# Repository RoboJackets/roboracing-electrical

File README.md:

# RoboRacing Electrical
This is a repository for the RoboJackets' RoboRacing Electrical team.

## rigatoni
Contains current files associated with Rigatoni.

## archive
Contains old files no longer in use on the current robots.

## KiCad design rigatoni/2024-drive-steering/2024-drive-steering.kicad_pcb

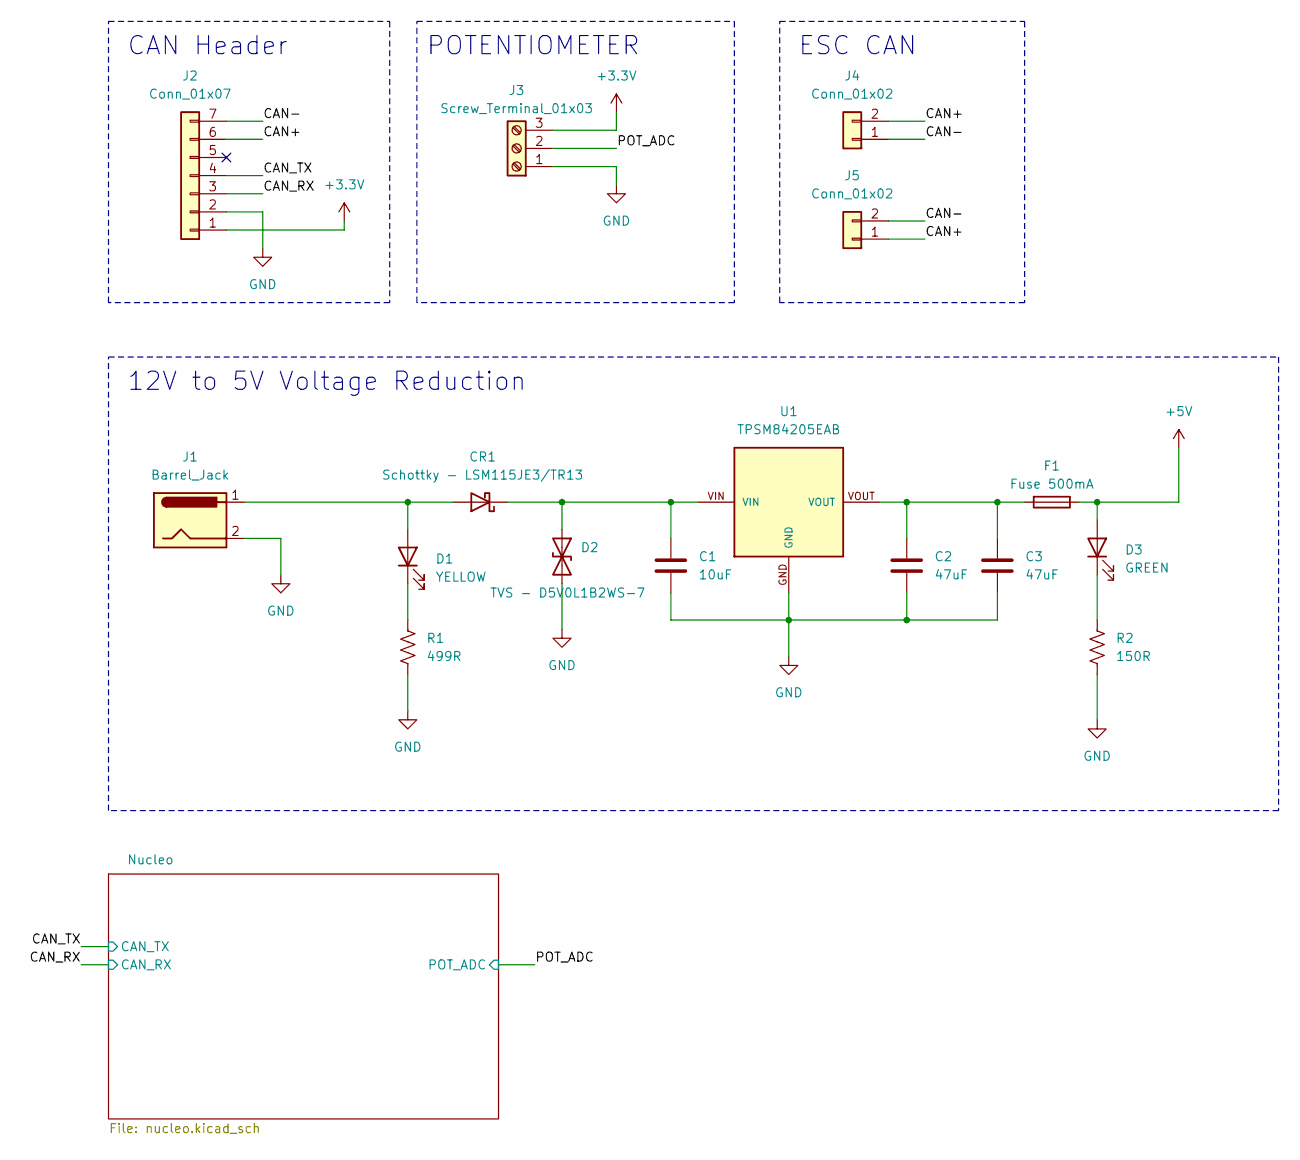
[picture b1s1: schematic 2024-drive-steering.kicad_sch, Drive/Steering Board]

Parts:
C1: 10uF; C_0805_2012Metric_Pad1.18x1.45mm_HandSolder; Part Name CL21A106KOQNNNE; DigiKey Part Number 1276-1096-1-ND
C2, C3: 47uF; C_1210_3225Metric_Pad1.33x2.70mm_HandSolder; Part Name CL32A476KOJNNNE; DigiKey Part Number 1276-3376-1-ND
CR1: Schottky - LSM115JE3/TR13; DO-214BA_MCH; Part Description Diode 15 V 1A Surface Mount DO-214BA; DigiKey Part Number 150-LSM115JE3/TR13CT-ND
D1: YELLOW; LED_0603_1608Metric_Pad1.05x0.95mm_HandSolder; Part Name 150060YS75000; DigiKey Part Number 732-4981-1-ND
D2: TVS - D5V0L1B2WS-7; D_SOD-323_HandSoldering; Part Description 14V Clamp 6A (8/20µs) Ipp Tvs Diode Sur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; DigiKey Part Number D5V0L1B2WS-7DICT-ND
D3: GREEN; LED_0603_1608Metric_Pad1.05x0.95mm_HandSolder; Part Name 150060GS75000; DigiKey Part Number 732-4971-1-ND
F1: Fuse 500mA; Fuse_0603_1608Metric_Pad1.05x0.95mm_HandSolder; Part Name C2Q 500; DigiKey Part Number 507-1089-1-ND
J1: Barrel_Jack; CUI_PJ-037A; Part Name PJ-037A; DigiKey Part Number CP-037A-ND
J2: Conn_01x07; CAN_Header
J3: Screw_Terminal_01x03; 282837-3_TYC; Part Name 282837-3; DigiKey Part Number A113321-ND
J4, J5: Conn_01x02; JST_PH_B2B-PH-K_1x02_P2.00mm_Vertical
R1: 499R; R_0603_1608Metric_Pad0.98x0.95mm_HandSolder; Part Name RC0603FR-07499RL; DigiKey Part Number 311-499HRCT-ND
R2: 150R; R_0603_1608Metric_Pad0.98x0.95mm_HandSolder; Part Name AC0603FR-07150RL; DigiKey Part Number YAG3568CT-ND
U1: TPSM84205EAB; Part Description Linear Regulator Replacement DC DC Conv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; DigiKey Part Number 296-47074-ND

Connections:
+3.3V: J2.1, J3.3; also elsewhere on the board
+5V: D3.2 (A), F1.1; also elsewhere on the board
/CAN+: J2.6, J4.2, J5.1
/CAN-: J2.7, J4.1, J5.2
/CAN_RX: J2.3; also elsewhere on the board
/CAN_TX: J2.4; also elsewhere on the board
/POT_ADC: J3.2; also elsewhere on the board
GND: C1.2, C2.2, C3.2, D2.2 (A2), J1.2, J2.2, J3.1, R1.1, R2.2, U1.GND; also elsewhere on the board
unnamed: C2.1, C3.1, F1.2, U1.VOUT
unnamed: CR1.2 (A), D1.2 (A), J1.1
unnamed: C1.1, CR1.1 (K), D2.1 (A1), U1.VIN
unnamed: D1.1 (K), R1.2
unnamed: D3.1 (K), R2.1

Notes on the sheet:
12V to 5V Voltage Reduction
ESC CAN
POTENTIOMETER
CAN Header

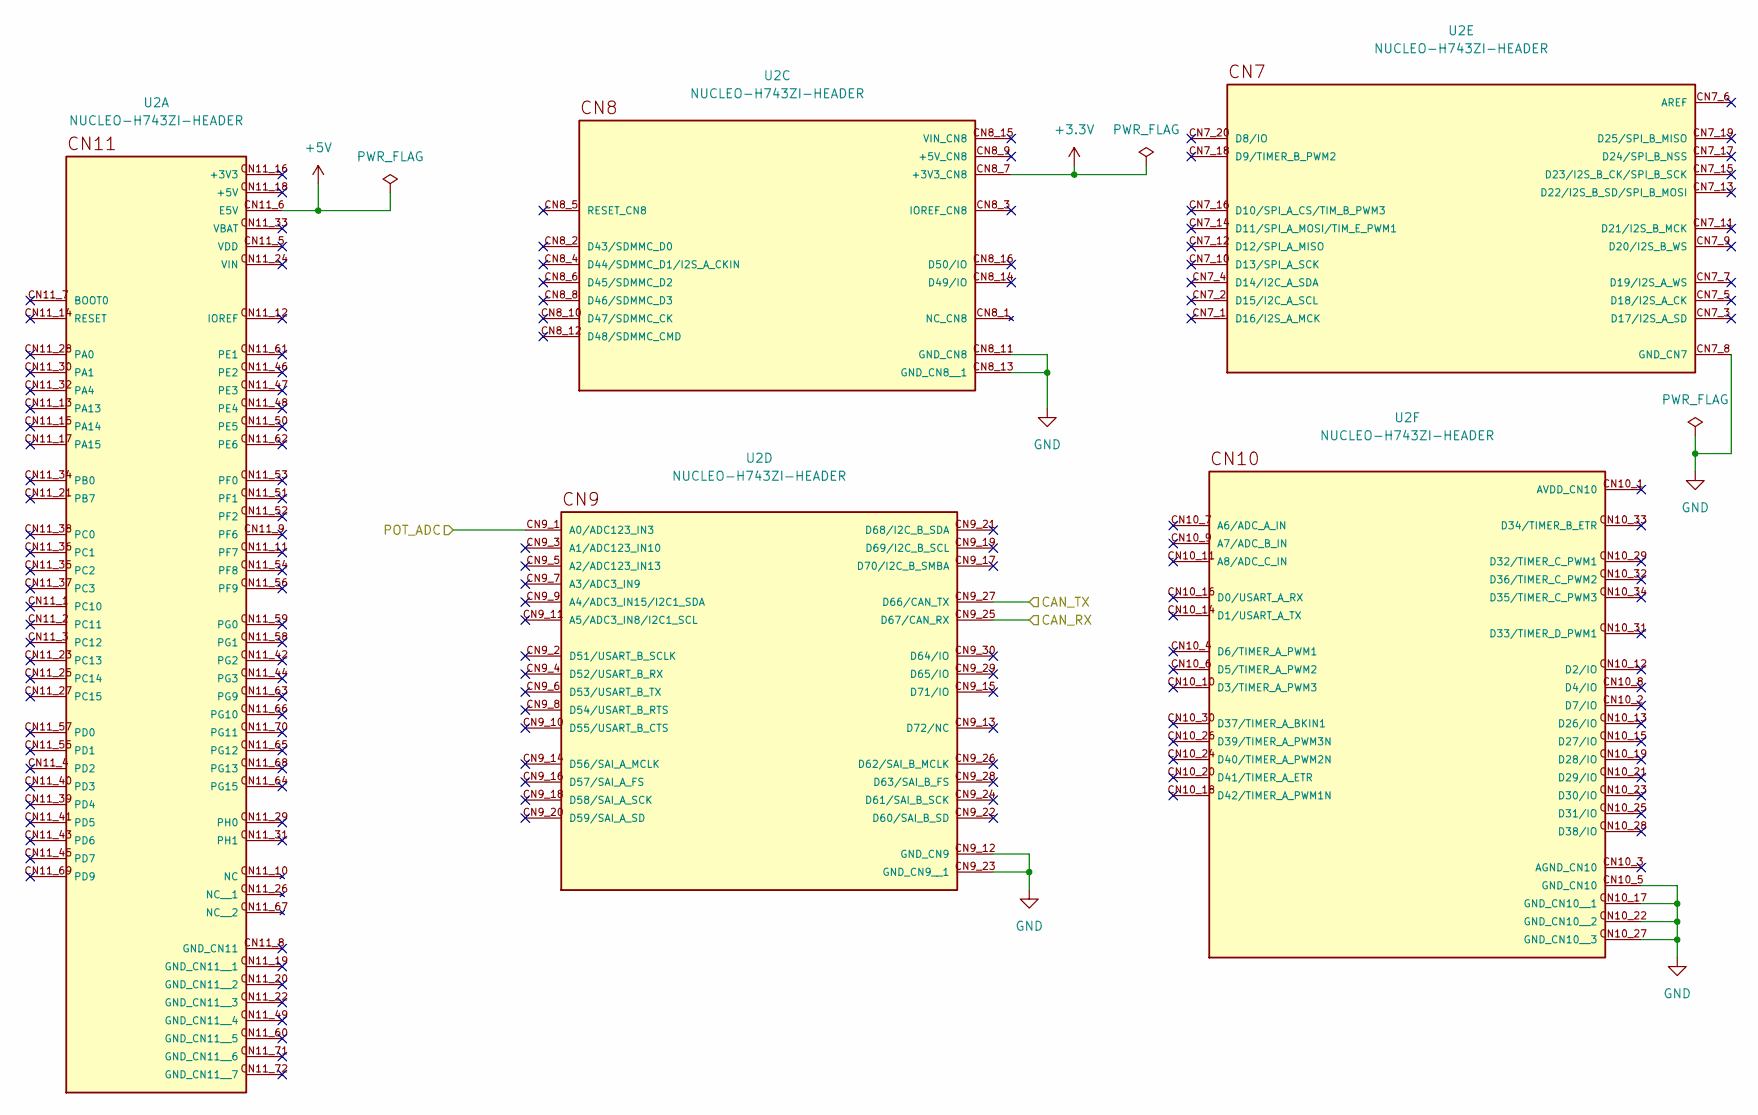
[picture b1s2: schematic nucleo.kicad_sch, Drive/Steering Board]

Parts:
U2: NUCLEO-H743ZI-HEADER; Custom-Nucleo144-Header; PARTREV 8

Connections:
+3.3V: U2.CN8_7 (+3V3_CN8); also elsewhere on the board
+5V: U2.CN11_6 (E5V); also elsewhere on the board
/CAN_RX: U2.CN9_25 (D67/CAN_RX); also elsewhere on the board
/CAN_TX: U2.CN9_27 (D66/CAN_TX); also elsewhere on the board
/POT_ADC: U2.CN9_1 (A0/ADC123_IN3); also elsewhere on the board
GND: U2.CN7_8 (GND_CN7), U2.CN8_11 (GND_CN8), U2.CN8_13 (GND_CN8__1), U2.CN9_12 (GND_CN9), U2.CN9_23 (GND_CN9__1), U2.CN10_5 (GND_CN10), U2.CN10_17 (GND_CN10__1), U2.CN10_22 (GND_CN10__2), U2.CN10_27 (GND_CN10__3); also elsewhere on the board

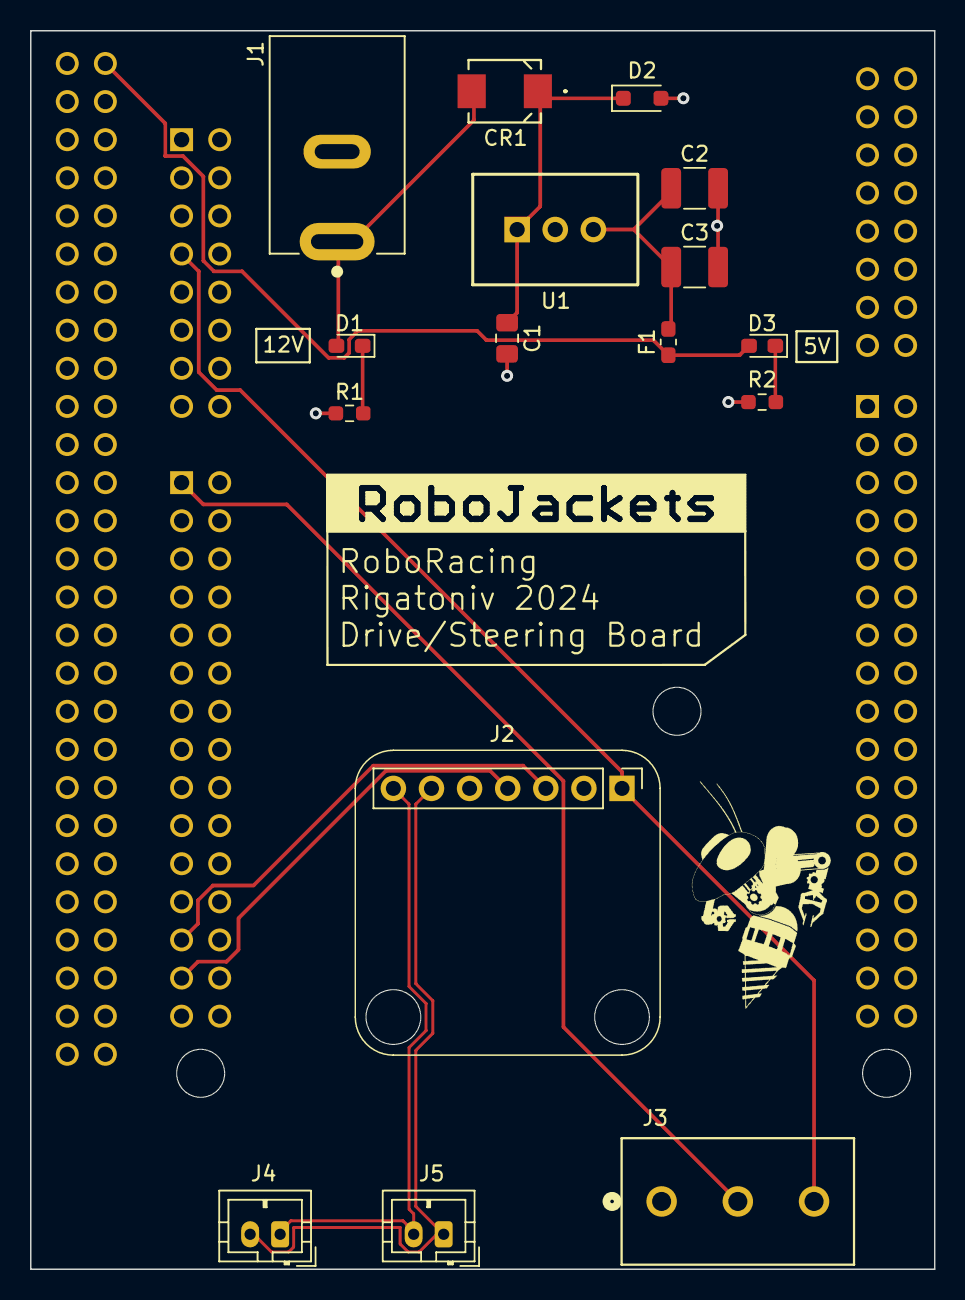
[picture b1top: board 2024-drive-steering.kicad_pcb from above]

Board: 2 copper layers, 60.2 x 82.5 mm, 17 parts (0 on the bottom side), 13 nets.

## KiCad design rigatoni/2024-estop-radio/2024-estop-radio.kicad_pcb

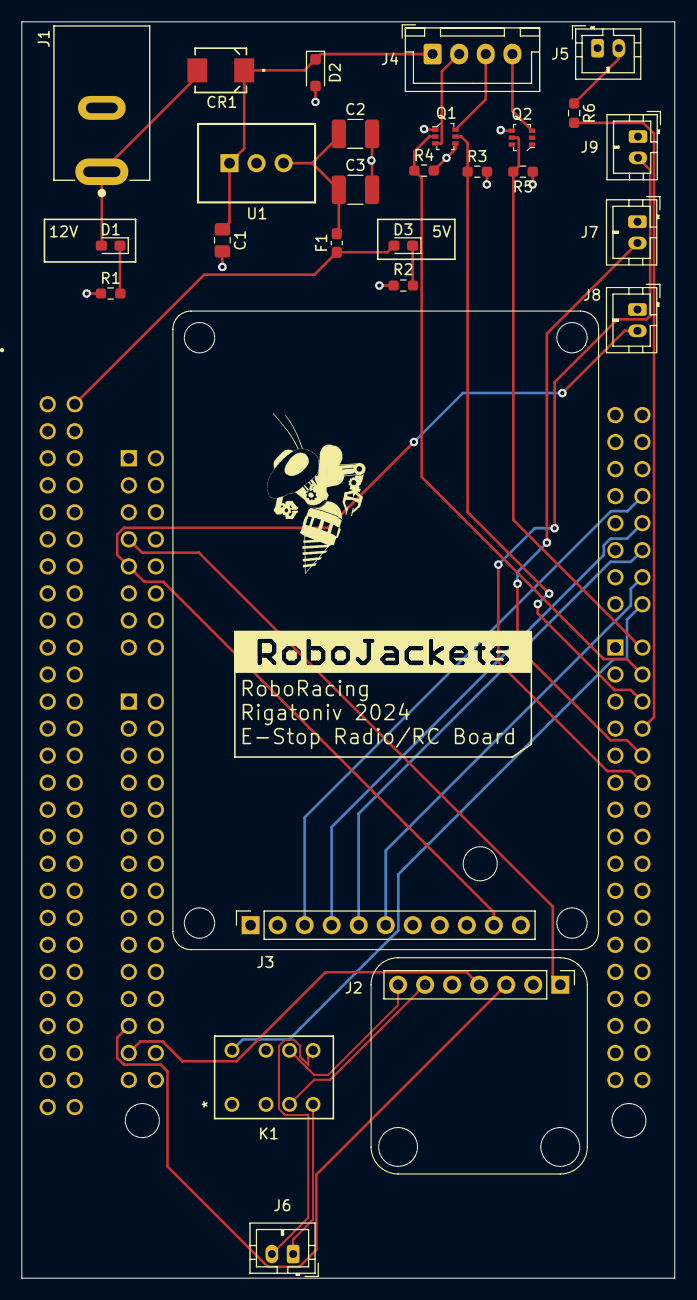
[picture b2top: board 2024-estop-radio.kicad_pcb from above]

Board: 2 copper layers, 61.4 x 118.1 mm, 28 parts (0 on the bottom side), 30 nets.

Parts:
C1: 10uF; C_0805_2012Metric_Pad1.18x1.45mm_HandSolder
C2, C3: 47uF; C_1210_3225Metric_Pad1.33x2.70mm_HandSolder
CR1: Schottky - LSM115JE3/TR13; DO-214BA_MCH
D1: YELLOW; LED_0603_1608Metric_Pad1.05x0.95mm_HandSolder
D2: TVS - D5V0L1B2WS-7; D_SOD-323_HandSoldering
D3: GREEN; LED_0603_1608Metric_Pad1.05x0.95mm_HandSolder
F1: Fuse 500mA; Fuse_0603_1608Metric_Pad1.05x0.95mm_HandSolder
J1: Barrel_Jack; CUI_PJ-037A
J2: Conn_01x07; CAN_Header
J3: Conn_01x11; E-Stop_Radio
J4: Conn_01x04; JST_XH_B4B-XH-A_1x04_P2.50mm_Vertical
J5, J6, J7, J8, J9: Conn_01x02; JST_PH_B2B-PH-K_1x02_P2.00mm_Vertical
K1: AGQ20003; RELAY_AGQ_PAN
Q1, Q2: BSS138DW-7-F; SOT-363
R1, R6: 499R; R_0603_1608Metric_Pad0.98x0.95mm_HandSolder
R2: 150R; R_0603_1608Metric_Pad0.98x0.95mm_HandSolder
R3, R4, R5: 10kR; R_0603_1608Metric_Pad0.98x0.95mm_HandSolder
U1: TPSM84205EAB
U2: NUCLEO-H743ZI-HEADER; Custom-Nucleo144-Header

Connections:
+3.3V: J2.1, U2.CN8_7 (+3V3_CN8)
+5V: J3.10, J8.2, U2.CN8_9 (+5V_CN8)
+12V: C1.1, CR1.1 (K), D2.1 (A1), J4.1, U1.VIN
/CAN_RX: J2.3, U2.CN9_25 (D67/CAN_RX)
/CAN_Relay: K1.8, U2.CN7_20 (D8/IO)
/CAN_TX: J2.4, U2.CN9_27 (D66/CAN_TX)
/Drive_Enable: J3.3, U2.CN7_12 (D12/SPI_A_MISO)
/Drive_RC: J9.2, U2.CN10_12 (D2/IO)
/E5V: D3.2 (A), F1.1, U2.CN11_6 (E5V)
/Estop_CAN+: J2.6, K1.3
/Estop_CAN-: J2.7, K1.6
/HV_Enable: R6.2, U2.CN10_8 (D4/IO)
/SW_CAN+: J6.1, K1.4
/SW_CAN-: J6.2, K1.5
/Safe_Estop: J3.6, U2.CN7_18 (D9/TIMER_B_PWM2)
/Stack_Light1: J4.2, Q1.3 (D1)
/Stack_Light2: J4.3, Q1.6 (D2)
/Stack_Light3: J4.4, Q2.3 (D1)
/Stack_MCU1: Q1.5 (G1), R3.1, U2.CN10_6 (D5/TIMER_A_PWM2)
/Stack_MCU2: Q1.2 (G2), R4.1, U2.CN10_4 (D6/TIMER_A_PWM1)
/Stack_MCU3: Q2.5 (G1), R5.2, U2.CN10_2 (D7/IO)
/Start_Estop: J3.5, U2.CN7_16 (D10/SPI_A_CS/TIM_B_PWM3)
/Steering_Enable: J3.4, U2.CN7_14 (D11/SPI_A_MOSI/TIM_E_PWM1)
/Steering_RC: J7.2, U2.CN10_10 (D3/TIMER_A_PWM3)
GND: C1.2, C2.2, C3.2, D2.2 (A2), J1.2, J2.2, J3.1, J3.11, J5.1, J7.1, J8.1, J9.1, K1.1, Q1.1 (S2), Q1.4 (S1), Q2.4 (S1), R1.1, R2.2, R3.2, R4.2, R5.1, U1.GND, U2.CN7_8 (GND_CN7), U2.CN8_11 (GND_CN8), U2.CN8_13 (GND_CN8__1), U2.CN9_12 (GND_CN9), U2.CN9_23 (GND_CN9__1), U2.CN10_5 (GND_CN10), U2.CN10_17 (GND_CN10__1), U2.CN10_22 (GND_CN10__2), U2.CN10_27 (GND_CN10__3)
unnamed: C2.1, C3.1, F1.2, U1.VOUT
unnamed: CR1.2 (A), D1.2 (A), J1.1
unnamed: D1.1 (K), R1.2
unnamed: D3.1 (K), R2.1
unnamed: J5.2, R6.1

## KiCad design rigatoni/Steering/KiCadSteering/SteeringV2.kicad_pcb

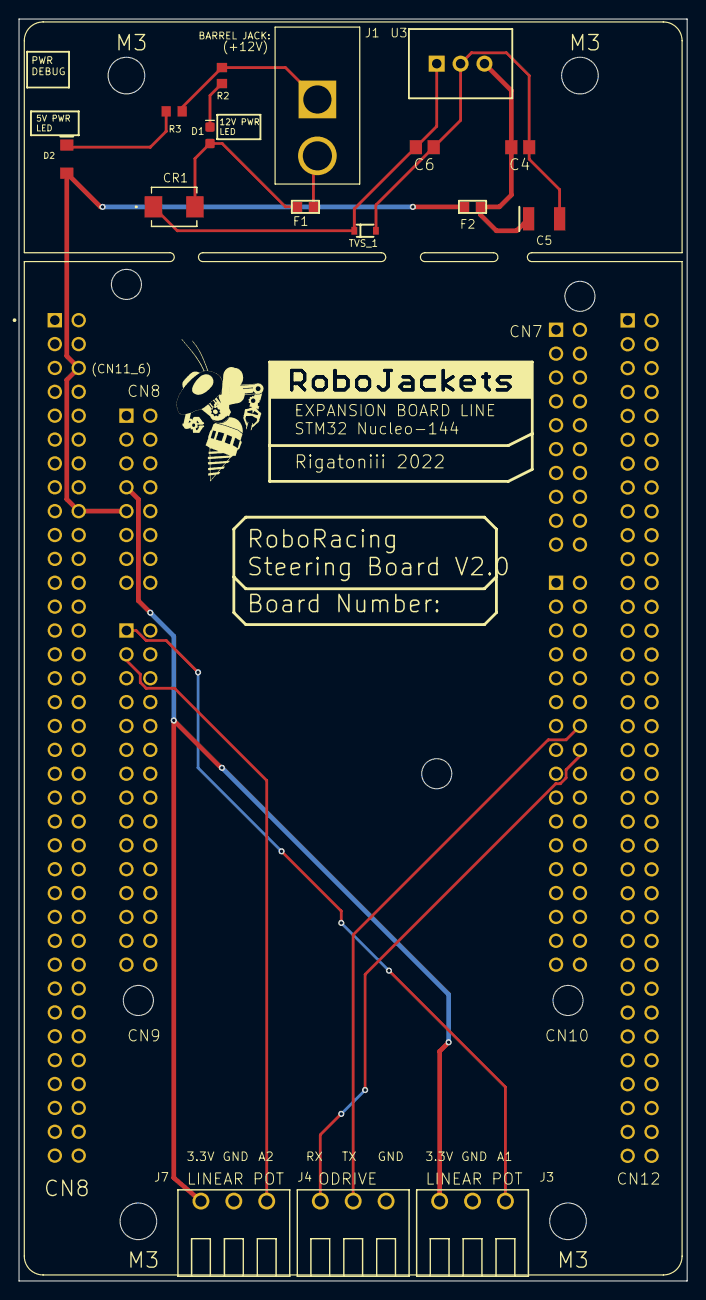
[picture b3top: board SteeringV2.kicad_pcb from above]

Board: 2 copper layers, 71.1 x 134.3 mm, 23 parts (0 on the bottom side), 13 nets.

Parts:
C4: 0.1uF; C0805
C5: 47uF; EIA3528
C6: 10uF; C0805
CR1: LSM115JE3/TR13; DO-214BA_MCH
D1: Yellow; LED-0603
D2: GREEN; LED-1206
F1: 630mA; F0603
F2: 1.875A; F0603
J1: PJ-037A
J3, J4, J7: PCB_SCREW_TERM_3; SCREW_TERMINAL_PCB_CONN_3_POLE
R2: 500R; R0603
R3: 147R; R0603
TVS_1: D5V0L1B2WS-7; SOD-323
U2: NUCLEO-H743ZI-HEADER; MODULE_NUCLEO-H743ZI
U3: TPSM84205EAB
U$1: ROBOBUZZ_0.8X
U$2, U$3, U$4, U$5: STANDOFF-HOLE
U$6: ROBOJACKETS

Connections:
5V_MAIN: C4.1, C5.A, F2.1, U3.VOUT
+3.3V: J3.1, J7.1, U2.CN8_7
+5V: D2.A, F2.2, U2.CN8_9, U2.CN11_6, U2.CN11_18
GND: C4.2, C5.C, C6.2, J1.P$1, J3.2, J4.3, J7.2, R2.1, R3.1, TVS_1.A, U2.CN7_8, U2.CN8_11, U2.CN8_13, U2.CN9_12, U2.CN9_23, U2.CN10_3, U2.CN10_5, U2.CN10_17, U2.CN10_22, U2.CN10_27, U2.CN11_8, U2.CN11_19, U2.CN11_20, U2.CN11_22, U2.CN11_49, U2.CN11_60, U2.CN11_71, U2.CN11_72, U2.CN12_9, U2.CN12_20, U2.CN12_32, U2.CN12_39, U2.CN12_54, U2.CN12_63, U2.CN12_71, U2.CN12_72, U3.GND
LINPOT_A1: J3.3, U2.CN9_1
LINPOT_A2: J7.3, U2.CN9_3
unnamed: CR1.2, D1.A, F1.2
unnamed: C6.1, CR1.1, TVS_1.C, U3.VIN
unnamed: F1.1, J1.P$2
unnamed: D1.C, R2.2
unnamed: D2.C, R3.2
USART_A_RX: J4.1, U2.CN10_16
USART_A_TX: J4.2, U2.CN10_14

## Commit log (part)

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2019-11-25 Updated board and schematic
    Changed encoder data to interrupt pin.
2019-11-25 Completed Routing for reivew
2019-11-25 Silkscreen and via adjustment
2019-11-25 Added constellated vias
2019-11-25 Added Status LED
2019-11-26 changed device led name
2019-11-26 Added indicator LED
2019-11-26 design review changes
2019-11-26 I'm not actually sure if anything has changed
2019-11-26 fixed some routing widths, added fuse values, etc
2019-11-26 fixed drc errors
2019-11-26 Changed file name and added schematic border
2019-11-26 Changed the library name, added 555 to library, implemented into both 'normal' and 'led' boards
2019-11-28 Board and CAD Updates
    -Made changes recommended in informal design review
    -Exported Board file to Inventor and continued CAD assembly
2019-12-01 Added Ethernet Poe Board CAD
2019-12-01 Continue updateding board and schematic with design review changes
2019-12-02 Mounting
    -Added CAD files for nearly entire assembly
    -Widened plastic mounting bracket
    -Added supporting ribs
    -Fileted everything to make it pretty
    -Fixed hole pattern in eth-poe
    -Fixed hole pattern in lower-right steering board mounting hole
2019-12-02 Fixed eth-poe footprint
    moved the holes on the ethernet-poe footprint down and in by 1mm in both the x and y directions, to match the existing state of the board
2019-12-02 Replaced Eth PoE board
    Hopefully now using the updated library w/ proper mounting hole locations
2019-12-02 Updated ethernet footprint
2019-12-02 Added holes under PoE mounting holes
2019-12-02 Fixed label style
2019-12-02 Board cleanup
    More room for zipties, cleaner routing, moved RC outline to bottom layer (where it will be placed)
2019-12-03 Receiver now completely under board
2019-12-03 Updated changes from design review
2019-12-03 Added second status LED
2019-12-03 Updated design review changes
2019-12-03 Made small silkscreen changes, moved usb to edge
2019-12-03 Turned off thermals
2019-12-03 Added documentation on tDocu layer
2019-12-03 changed name of Estop_Daughterboard folder
2019-12-03 test folder added
2019-12-03 moved test folder into new-cari
2019-12-03 changed readme
2019-12-03 Finished routing new connecters
2019-12-03 Fixed USB routing widths
2019-12-04 made some minor a e s t h e t i c tweaks to the board layout
2019-12-07 added crystal to BOM
2019-12-30 making sure right part number in sheet
2020-01-05 Fall design review changes pt1
2020-01-07 Fall design review changes pt3
2020-01-07 moved the estop_motherboard file from Estop_daugherboard to Estop_Daugherboard
2020-01-07 Some design review changes
2020-01-08 Design review changes 1
2020-01-08 Design review changes 2
2020-01-08 Button implemented in hardware through AND gates
2020-01-09 Post-Design Review Board Changes
2020-01-09 Edited ethernet library part to have 44.5mm width and 40.64mm spacing to allow mating to 0.1in headers
2020-01-09 passing DRC now
2020-01-09 Made some minor adjustments
2020-01-09 Fixed supply symbol for 5V input
2020-01-10 Label changes to schematic
    Also trying to add another pin to the reciever so we can see when it's plugged in
2020-01-10 Button changed to NO w/ pulldown resistor, inputs to MCU changed to IN signals
2020-01-10 Brake_en moved to PWM pin on mcu
2020-01-10 Update from review 2
2020-01-10 Fixed labels and orientation of RJ Logo
2020-01-11 Added digikey part number attribute to most parts
2020-01-12 test
2020-01-12 added CAM file
2020-01-12 Added fuse current rating estimation
    Check design review doc for potential concerns
2020-01-14 Create control_board_3.3_parts.csv
    Rearranged some column orders on the BOM
2020-01-14 Removed Pink LED
    Sorry Kyle
2020-01-14 did absolutely nothing
2020-01-14 Update control_board_3.3_parts.csv
    Added quantity per board column
2020-01-14 Create sedani_chassis_control_2020-01-14.zip
    Made CAM file
2020-01-14 added throttle and switch connectors
2020-01-14 Updated resistive bridge with cap to gnd
2020-01-14 Cleaned up schematic and board
2020-01-18 added new ethernet jack part
2020-01-18 changed ethernet jack and rerouted
2020-01-20 removed arduino folder
2020-02-18 did an inventory
2020-02-19 finished to order list
2020-03-29 Added LED Cube personal project
2020-03-29 Removed extraneous file
2020-04-06 Replaced Non-Assmann VGA connector with TE one
    Look it's not pretty but it's 2 AM routing. It'll do the job.
2020-04-06 fixed readme
2020-04-06 Improved documentation on schematic
2020-04-13 Updated SCNN pin
2020-04-13 Updated CS_ETH pin
2020-04-13 Fixed USB to ground
2020-05-24 Updating description of LDO
2020-05-25 Added more parts to library, cleaned up board and schematic
2020-05-26 Added termination of ethernet taps
2020-06-15 Updated symbols to Style Guide standards
2020-06-23 Updated to Style Guide Standards
2020-06-26 First routing and layout pass completed.
2020-06-26 Updated poe library with oscillator
2020-06-27 Updated Steering library to style guide standards
2020-06-28 Updated board_outline library to style guide standards
2020-06-28 Updated EVGP_Estop_Motherboard library to style guide standards
2020-06-28 Updated neopixel_board library to style guide standards
2020-06-28 Updated WIZ850io library to style guide standards
2020-07-07 updates
    -added grounded mounting holes
    - added ground and stich capacitor for SPI line return current
    - added some polygons
    - fixed several DRC errors
2020-07-08 Actually finished changes for eFuse schematic
2020-07-11 routing for efuse
2020-07-12 Pre Review Commit, Completed Routing
2020-07-12 added DRC
2020-07-12 Made drc compliant
2020-07-25 Began design review changes
2020-08-03 post design review routing updates
    replaced 5V DC/DC converter catch diode
    routed Wiznet LEDs
    added thermal pads to efuse and DC/DC converters
2020-08-07 added top board with wiznet port
2020-08-24 Changed capacitor for load
2020-08-24 Updated more values based on availability
2020-09-19 Revert "Delete ethernet_poe.lbr to resolve conflict"
    This reverts commit ef95645cfb66f80d5ac58dd1acb75e853ce7e5ff.
2020-10-11 Setup initial library
2020-10-15 Made v2.1, updated initial problems on library, sch
2020-10-18 Cleaned up some labels
2020-10-18 Library Contains SP3003-02
    Created the SP3003-02 part in Eagle.
2020-10-25 Added ESD224 part to the library
2020-10-25 Added DKPN and implemented stylistic fixes
2020-11-01 copied over circuit blocks from Estop motherboard
2020-11-02 got rid of empty project file
2020-11-07 Committing TPS70625DBVR Part
    Finished Part.
2020-11-07 Committed LM26420XMH Part.
2020-11-08 Added library with USB and HDMI Control
2020-11-08 Sylistic change in Symbol for LM26420XMH
2020-11-08 Committed XS10 (Compute Header)
2020-11-08 Committed LAN9513-JZX
2020-11-08 Began raspberry pi compute
2020-11-09 Finished Raspberry Pi Compute
2020-11-17 Added headers to board and rough board layout.
2020-11-22 Added bidirectional level shifters for 3.3v SPI and I2C connectivity
2020-11-22 Updated Capacitors/Resistors
2020-11-23 repositioned some headers
2020-12-04 Finished board changes
2020-12-04 Removed old manufacturing files
2021-01-08 Fixed Silkscreen, added header pinout, misc touchups
2021-01-16 Finished Page 3, Re-working Page 1
2021-01-17 more fixes
2021-01-18 passing drc except for header errors
2021-01-22 Disb Vision Library Edit/Schematic Update
    Edited Pins 4,6,10,12,14,16,18,22,24 to SDX_ for MicroSD
    Finish Micro_SD part of Schematic on Pg 1
    Replaced BJT with JP1 on Pg 3
2021-01-23 Corrected FB1 Label Issue
2021-01-24 Added Page 2 of StereoPi Schematic
2021-01-31 Combined all Schematic Pages
    Fixed some Capacitor/Resistor Values
    Began integrating POE
2021-02-01 moved usb, trace under label, and stray line on silkscreen
2021-02-07 Cleaning up Schematic
2021-02-07 Integrated PoE
2021-02-14 Added schematic files for speedometer
2021-02-21 Cleaned up Schematic/Worked on Board
2021-03-07 added components etc to BOM
2021-03-07 with BOM
2021-03-21 Board/Schematic Update
2021-03-21 Schematic/Board
2021-04-26 This is some firmware that plots the radar position and velocity data
2021-05-15 Version 3
2021-05-15 Joe Cleanup Schematic
2021-05-16 Updated Values in DisbVision sch
2021-05-16 Routed Board Based off Schematic Changes
2021-05-16 Updated Gerber
2021-05-17 Added pick and place
2021-05-17 BOM/PnP Changes
2021-07-11 Created Speedometer board
    Created board file and removed other unused files
2021-07-11 Added RoboBuzz/RoboJackets symbols on board
2021-07-14 Updated board and gerber files
2021-10-24 Made CSV so git trackable
2021-10-24 Cleanup for merge
2021-10-24 Restored deleted files
2021-10-24 Updates readme
2021-10-24 Remove DS_Store
2021-12-05 Added battery monitor schematic and board layout
    Work in progress
2021-12-05 Fix R1 value
2021-12-12 First Draft Done!
2022-01-16 E-stop-radio board created (Rough)
    Still in the process of rearranging the components.
2022-01-18 Steering Schematic Draft 1
2022-01-21 Switched out old Nucleo Header with updated one that has Morpho Connectors Integrated
2022-01-22 Integrated new header symbols and updated power circuitry on steering schematic
2022-01-23 Create DESCRIPTION
2022-01-23 Create QSH-030-01-X-D-A-XX.lbr
    Added library for LCD female connector
2022-01-23 Updated power circuitry
2022-01-24 Added 12V to 5V power circuit and LCD connector to schematic
    Started to assign pins between the LCD connector and the nucleo header pins
2022-01-28 with copy files
2022-01-29 with headers and TVS
2022-01-30 Committed for Archie/Advaith
2022-01-31 eStopV2 Rough Draft Complete
    Optimization is still needed
2022-02-01 Finished Rough Draft for Schematic Review
    Not updated with changes suggested during schematic review
2022-02-04 Implemented changes from schematic review
    LED Connector and Power Circuitry still needs to be updated in schematic
2022-02-04 Steering Schematic Updated After Internal Design Review
2022-02-05 Adjusted some placement
2022-02-05 Started routing the board
    LED connector still not completed
2022-02-13 Completed routing for v1.0
    Removed LED connector and ready for design review
2022-02-20 Uploading Library and Eagle Schematic
2022-02-20 Cleaned up schematic and board
    Removed unused library and updated out of stock/not sold components
2022-02-23 Cleaned up
2022-02-23 Board Cleanup
2022-02-24 Cleaned up brd
2022-02-26 Schematic Design
    Schematic Design updated and components changed
2022-02-27 Footprint Update
    Updated Footprints for receiver and RGB light
2022-03-14 Moved Files to Correct Branch
    moved files from ecosystem to john branch
2022-03-14 Manual Board Update
    Ran DRC on board and fixed errors
2022-03-15 Gerber File
    Gerber File added to folder
2022-03-15 Board update
    Updates silkscreen and trace widths
2022-03-15 cam data and silkscreen
    Generated CAM data and updated silkscreen
2022-04-06 Fixed Gerber Files
    Created new Gerber File for manual Board
2022-11-23 Updated Board
    Changed Transeiver Holes and Spacing and RGB LED holes and spacing
2023-11-12 Add start of STM schematic
2023-11-12 Remove unnecessary KiCad files
2024-01-23 removed unnecessary parts and imported from eagle to kicad
2024-04-07 Added some changes to CAN header board for Nucleo
2024-04-12 Finished CAN to Ethernet PCB Header for Nucleo
2024-04-12 Added some RoboJackets theming
2024-04-16 Completed PCBs for 2024
